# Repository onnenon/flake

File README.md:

<div align="center">
    
    <h3>Anywhy Flake</h3>
    <p><i>Minimalism, efficiency and comfort</i></p>
</div>

# Why

_To be productive, stay healthy and enjoy the process._

By the 19th century, a need for a faster way of writing had emerged, which led to the invention of typewriters. Two centuries later, modern keyboards don't look much different from their predecessors, even though such design has been proven to be quite inefficient and often harmful.

Addressing these problems leads to huge benefits considering how often people use keyboards in the modern world.

# How

There are several problems that the Flake keyboard solves. I'll describe those with the most significant impact.

## Stagger

If you take your hand and look at the fingers, you can notice that they are positioned horizontally. Now take a look at your keyboard - the keys are grouped in arrays that are shifted vertically, known as row-based stagger.

This well-known layout forces your fingers to move in a counterintuitive way. The solution to that problem is simple: we need to rearrange the keys in a more human-friendly way.

As you can see, Flake has what's called a column-based stagger. Because of this, keys are located in the path of natural finger movement, which results in a much more pleasant typing experience and reduced fatigue.

## Split

One of the most noticeable things about Flake is that it has two separate halves.

Regular keyboards are made in a single monolithic block, and the main problem is that such a form factor requires our forearms to meet in the center. To compensate for this, wrists are bent apart. This position creates an unnatural angle between the forearm and the wrist, which in the long term will likely lead to constant wrist pain.

Each half of the split keyboard can be rotated and placed in any suitable way so everyone can adapt the setup to their personal preference, avoiding potential damage to the wrists.

As an added bonus, we get free space right between the halves which can be occupied by a trackpad, coffee, or even a cat (=^..^=).

## Keys amount

There's a high chance that some might feel confused seeing such a small number of keys, considering user productivity is one of the priorities for Anywhy.

Indeed, Flake has fewer keys than most conventional keyboards (46 keys in total), and that's not a compromise, but a feature. A large number of keys causes hands to move around to reach further-placed keys like digits, brackets, punctuation, Backspace, Escape, etc.

Having fewer keys doesn't mean less functionality. In fact, Flake is not only fully input-compatible with regular keyboards but also allows you to add more keys than most keyboards have.

By default, Flake uses [ZMK Firmware](https://zmk.dev) which provides functionality that significantly increases productivity. One of the most used features, which allows having all possible inputs with a minimal amount of keys, is [layers](https://zmk.dev/docs/keymaps#layers). They are pretty simple and work just like the well-known Shift key.

For those who strive for absolute comfort and compactness, there is also Flake S with 40 keys.

The small version lacks one outer column on each of the halves to reduce pinky usage, as it is the weakest of all fingers.

## Thumb cluster

Keyboards are used in various ways, not only for typing text. Most popular tasks require the use of mod keys such as Control, Alt/Option, Super/Command/Win, and of course, Shift. Even though these keys are regularly used, they are placed in ridiculously inconvenient spots where only the pinky can reach them, and as we already know, it's the weakest finger.

The Flake keyboard has a so-called thumb cluster which contains 10 keys in total to address that problem. In contrast, the thumb is one of the strongest fingers and is ideal for holding mod keys.

# What

Flake supports both wired and wireless (Bluetooth) connection, which makes it perfect for both home usage with a PC or portable setup with a laptop, tablet, or even smartphone.

To achieve both types of connectivity, each half has two USB-C ports, one on the top and one on the inner side. The side port is used to connect the halves together, and then one of them (usually the left one) can be connected to any device using the top port, which is also used to charge the keyboard.

> Ports on the side are used only to communicate with each other, so they can't be used to charge the keyboard or to flash the new firmware
> 

Flake is extremely thin. The keyboard body without switches and feet is a bit less than 0.8cm in height, which makes it compact and really comfortable to use, especially with low-profile switches.

> Unfortunately, to achieve such a low height, some tradeoffs were made in PCB and enclosure designs that make assembly and soldering a bit tricky. There's a chance that the keyboard will become thicker in the future if it will make it more robust and easier to repair.

Talking about switches, Flake is hot-swappable and supports three types of switches: the well-known Cherry MX compatible switches, low-profile Kailh Choc V1, and their newer version Choc V2.

In order to use MX Switches, the special "plate" comes with the Flake which should be placed between the board and the switches.

> Plates are not required for the Choc switches as they are much lower than MX switches and don't need additional enclosure height to securely sit in the board

Anywhy Flake v0.1.0 is fully the tested version. The most similar version this repo has is v0.1.1, where I've changed the silkscreen modified some edges, and also added PCB copper fill. So if you want to build Flake yourself, I recommend using the v0.1.1 version, as well as checking out the [build guide](/docs/build_guide.md)

> Feel free to send me your builds and keyboard reviews :)

# Credits

Huge thanks to:

- [@foostan](https://github.com/foostan), the author of [Corne Keyboard](https://github.com/foostan/crkbd) which was my introduction to the world of ergonomic keyboards.
  
- [@pashutk](https://github.com/pashutk), the author of [Chocofi](https://github.com/pashutk/chocofi), an amazing tiny keyboard I've been using for a while.
  
- [@josefadamcik](https://github.com/josefadamcik), the author of [Sofle](https://github.com/josefadamcik/SofleKeyboard) which gave huge inspiration for the Flake's key layout.
  
- [@petejohanson](https://github.com/petejohanson) for creating [ZMK Firmware](https://github.com/zmkfirmware/zmk) and all the [contributors](https://github.com/zmkfirmware/zmk/graphs/contributors) that make it better each day.

- Everyone working on [KiCad](https://gitlab.com/kicad/code/kicad) and [FreeCAD](https://github.com/FreeCAD/FreeCAD), for creating such powerful open source tools

- People from the [ZMK discord server](https://zmk.dev/community/discord/invite) for being so kind while helping me learn how to design PCB and how to debug and solve various problems.

- Finally, a huge thank you to everyone who explores unpopular technologies, digs into niche topics, and makes amazing things possible.

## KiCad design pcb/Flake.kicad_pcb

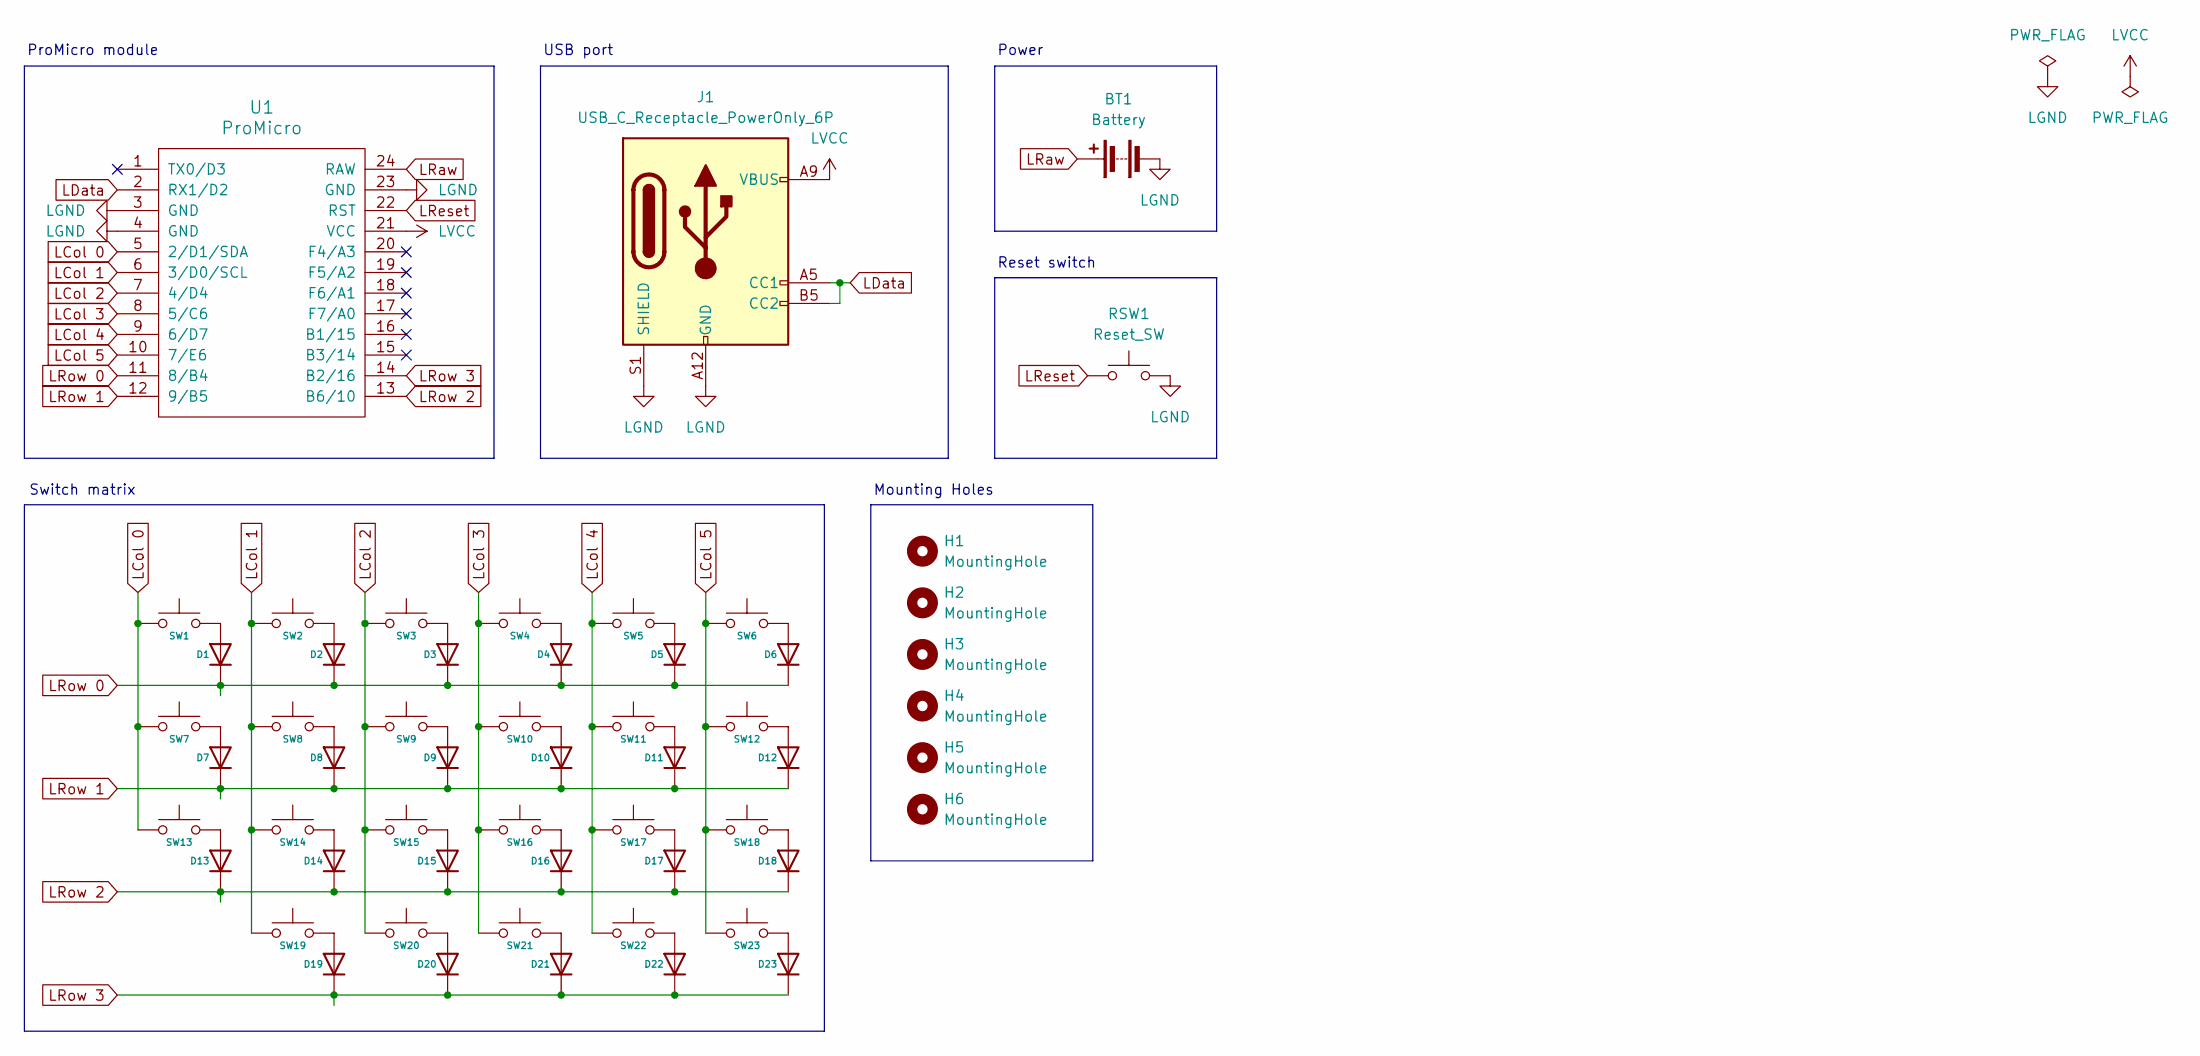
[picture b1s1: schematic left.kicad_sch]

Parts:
BT1: Battery; JST_1.25mm_mid-mount
D1, D2, D3, D4, D5, D6, D7, D8, D9, D10, D11, D12, D13, D14, D15, D16, D17, D18, D19, D20, D21, D22, D23: D; D_SOD-123_Handsoldering
H1, H2, H3, H4, H5, H6: MountingHole; MountingHole_2.2mm_M2
J1: USB_C_Receptacle_PowerOnly_6P; USB-C_6Pin_Mid-mount
RSW1: Reset_SW; TS-1289VE-4
SW1, SW2, SW3, SW4, SW5, SW6, SW7, SW8, SW9, SW10, SW11, SW12, SW13, SW14, SW15, SW16, SW17, SW18, SW19, SW20, SW21, SW22, SW23: SW_Push; SW_MX_Choc-v1v2_Hotswap
U1: ProMicro; ProMicro_SMD

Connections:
LCol 0: SW1.1, SW7.1, SW13.1, U1.5 (2/D1/SDA)
LCol 1: SW2.1, SW8.1, SW14.1, SW19.1, U1.6 (3/D0/SCL)
LCol 2: SW3.1, SW9.1, SW15.1, SW20.1, U1.7 (4/D4)
LCol 3: SW4.1, SW10.1, SW16.1, SW21.1, U1.8 (5/C6)
LCol 4: SW5.1, SW11.1, SW17.1, SW22.1, U1.9 (6/D7)
LCol 5: SW6.1, SW12.1, SW18.1, SW23.1, U1.10 (7/E6)
LData: J1.A5 (CC1), J1.B5 (CC2), U1.2 (RX1/D2)
LGND: BT1.2 (-), J1.A12 (GND), J1.B12 (GND), J1.S1 (SHIELD), RSW1.2, U1.3 (GND), U1.4 (GND), U1.23 (GND)
LRaw: BT1.1 (+), U1.24 (RAW)
LReset: RSW1.1, U1.22 (RST)
LRow 0: D1.1 (K), D2.1 (K), D3.1 (K), D4.1 (K), D5.1 (K), D6.1 (K), U1.11 (8/B4)
LRow 1: D7.1 (K), D8.1 (K), D9.1 (K), D10.1 (K), D11.1 (K), D12.1 (K), U1.12 (9/B5)
LRow 2: D13.1 (K), D14.1 (K), D15.1 (K), D16.1 (K), D17.1 (K), D18.1 (K), U1.13 (B6/10)
LRow 3: D19.1 (K), D20.1 (K), D21.1 (K), D22.1 (K), D23.1 (K), U1.14 (B2/16)
LVCC: J1.A9 (VBUS), J1.B9 (VBUS), U1.21 (VCC)
unnamed: D1.2 (A), SW1.2
unnamed: D2.2 (A), SW2.2
unnamed: D3.2 (A), SW3.2
unnamed: D4.2 (A), SW4.2
unnamed: D5.2 (A), SW5.2
unnamed: D6.2 (A), SW6.2
unnamed: D7.2 (A), SW7.2
unnamed: D8.2 (A), SW8.2
unnamed: D9.2 (A), SW9.2
unnamed: D10.2 (A), SW10.2
unnamed: D11.2 (A), SW11.2
unnamed: D12.2 (A), SW12.2
unnamed: D13.2 (A), SW13.2
unnamed: D14.2 (A), SW14.2
unnamed: D15.2 (A), SW15.2
unnamed: D16.2 (A), SW16.2
unnamed: D17.2 (A), SW17.2
unnamed: D18.2 (A), SW18.2
unnamed: D19.2 (A), SW19.2
unnamed: D20.2 (A), SW20.2
unnamed: D21.2 (A), SW21.2
unnamed: D22.2 (A), SW22.2
unnamed: D23.2 (A), SW23.2

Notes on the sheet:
Switch matrix
Mounting Holes
USB port
Power
ProMicro module
Reset switch

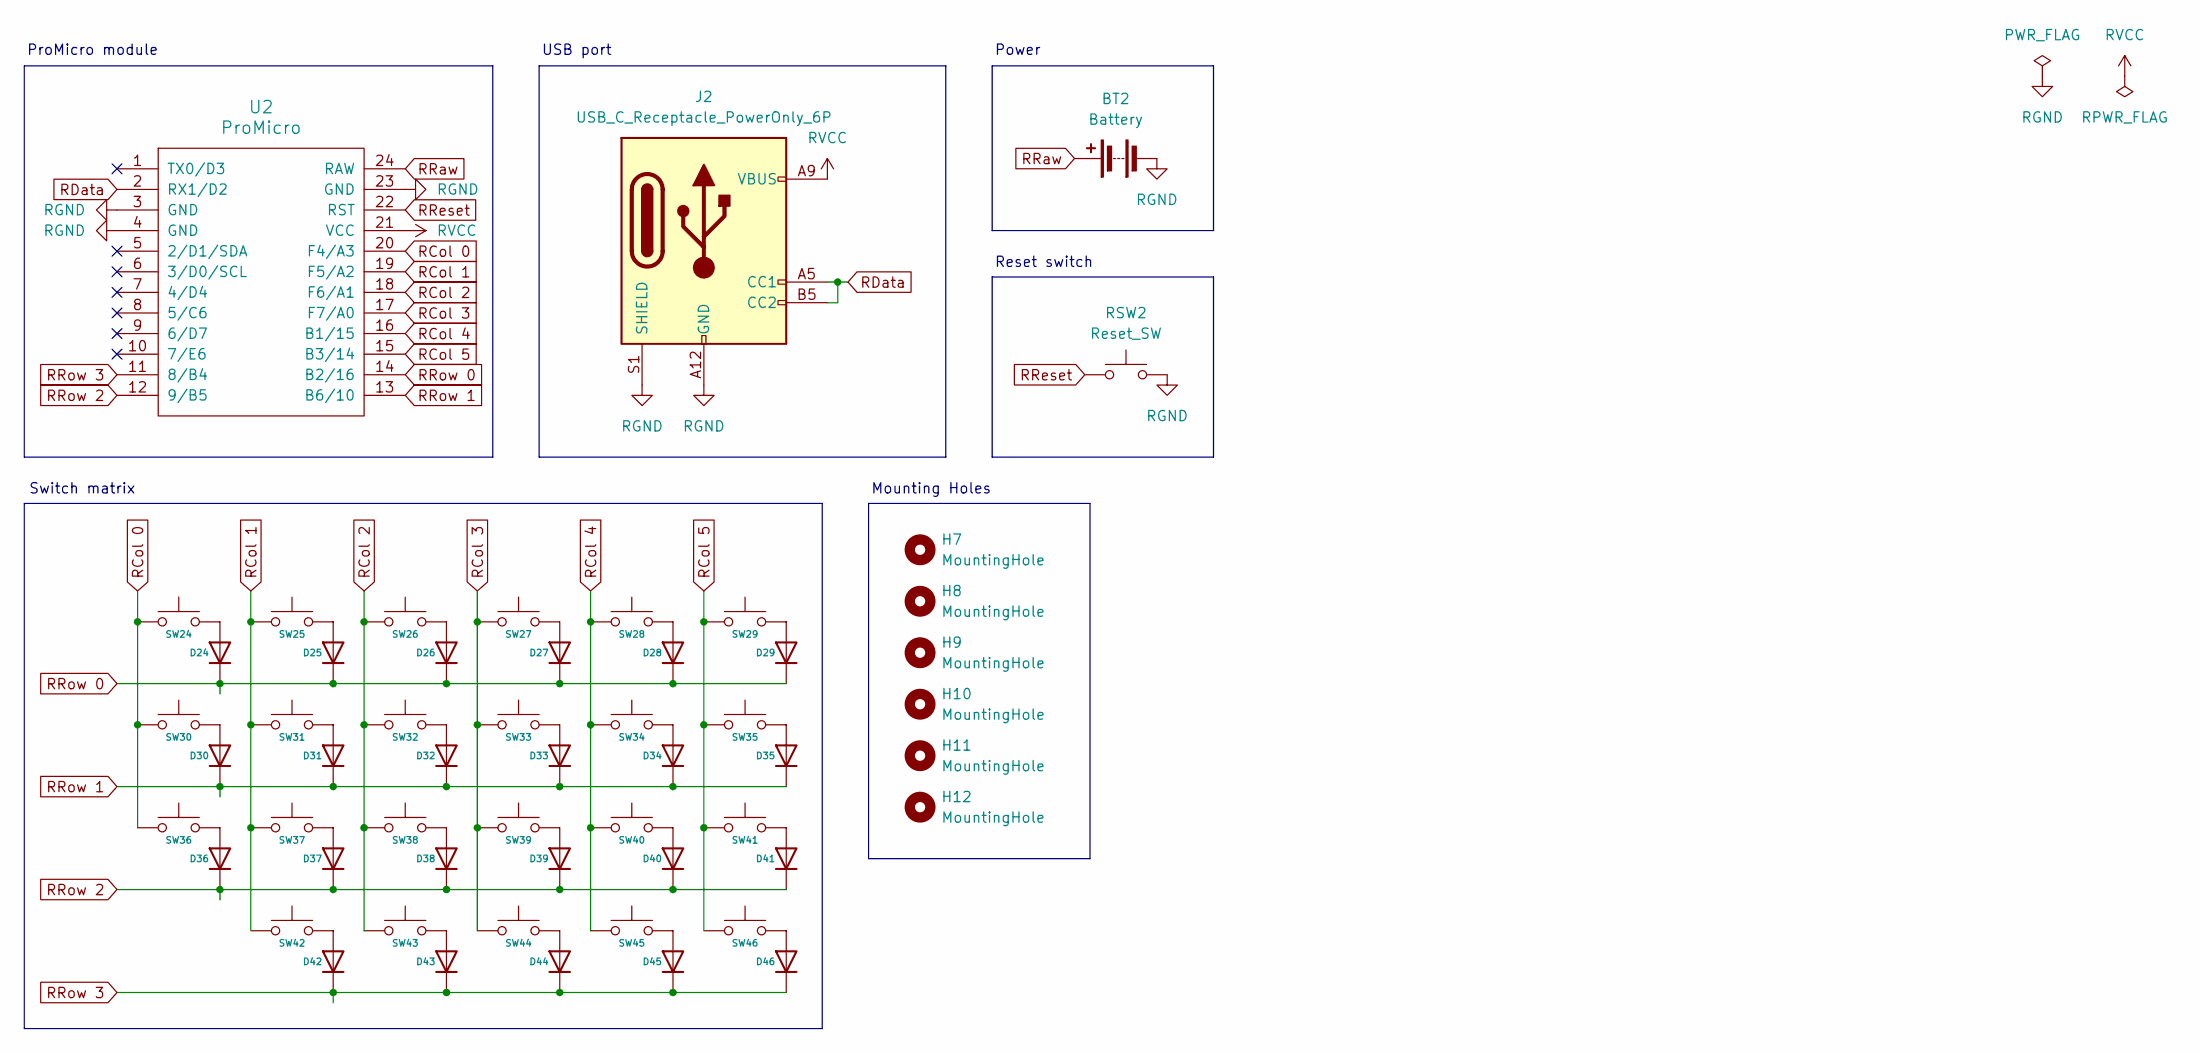
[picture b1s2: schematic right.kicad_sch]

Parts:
BT2: Battery; JST_1.25mm_mid-mount
D24, D25, D26, D27, D28, D29, D30, D31, D32, D33, D34, D35, D36, D37, D38, D39, D40, D41, D42, D43, D44, D45, D46: D; D_SOD-123_Handsoldering
H7, H8, H9, H10, H11, H12: MountingHole; MountingHole_2.2mm_M2
J2: USB_C_Receptacle_PowerOnly_6P; USB-C_6Pin_Mid-mount
RSW2: Reset_SW; TS-1289VE-4
SW24, SW25, SW26, SW27, SW28, SW29, SW30, SW31, SW32, SW33, SW34, SW35, SW36, SW37, SW38, SW39, SW40, SW41, SW42, SW43, SW44, SW45, SW46: SW_Push; SW_MX_Choc-v1v2_Hotswap
U2: ProMicro; ProMicro_SMD

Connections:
unnamed: D24.2 (A), SW24.2
unnamed: D25.2 (A), SW25.2
unnamed: D26.2 (A), SW26.2
unnamed: D27.2 (A), SW27.2
unnamed: D28.2 (A), SW28.2
unnamed: D29.2 (A), SW29.2
unnamed: D30.2 (A), SW30.2
unnamed: D31.2 (A), SW31.2
unnamed: D32.2 (A), SW32.2
unnamed: D33.2 (A), SW33.2
unnamed: D34.2 (A), SW34.2
unnamed: D35.2 (A), SW35.2
unnamed: D36.2 (A), SW36.2
unnamed: D37.2 (A), SW37.2
unnamed: D38.2 (A), SW38.2
unnamed: D39.2 (A), SW39.2
unnamed: D40.2 (A), SW40.2
unnamed: D41.2 (A), SW41.2
unnamed: D42.2 (A), SW42.2
unnamed: D43.2 (A), SW43.2
unnamed: D44.2 (A), SW44.2
unnamed: D45.2 (A), SW45.2
unnamed: D46.2 (A), SW46.2
RCol 0: SW24.1, SW30.1, SW36.1, U2.20 (F4/A3)
RCol 1: SW25.1, SW31.1, SW37.1, SW42.1, U2.19 (F5/A2)
RCol 2: SW26.1, SW32.1, SW38.1, SW43.1, U2.18 (F6/A1)
RCol 3: SW27.1, SW33.1, SW39.1, SW44.1, U2.17 (F7/A0)
RCol 4: SW28.1, SW34.1, SW40.1, SW45.1, U2.16 (B1/15)
RCol 5: SW29.1, SW35.1, SW41.1, SW46.1, U2.15 (B3/14)
RData: J2.A5 (CC1), J2.B5 (CC2), U2.2 (RX1/D2)
RGND: BT2.2 (-), J2.A12 (GND), J2.B12 (GND), J2.S1 (SHIELD), RSW2.2, U2.3 (GND), U2.4 (GND), U2.23 (GND)
RRaw: BT2.1 (+), U2.24 (RAW)
RReset: RSW2.1, U2.22 (RST)
RRow 0: D24.1 (K), D25.1 (K), D26.1 (K), D27.1 (K), D28.1 (K), D29.1 (K), U2.14 (B2/16)
RRow 1: D30.1 (K), D31.1 (K), D32.1 (K), D33.1 (K), D34.1 (K), D35.1 (K), U2.13 (B6/10)
RRow 2: D36.1 (K), D37.1 (K), D38.1 (K), D39.1 (K), D40.1 (K), D41.1 (K), U2.12 (9/B5)
RRow 3: D42.1 (K), D43.1 (K), D44.1 (K), D45.1 (K), D46.1 (K), U2.11 (8/B4)
RVCC: J2.A9 (VBUS), J2.B9 (VBUS), U2.21 (VCC)

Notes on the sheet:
Switch matrix
Mounting Holes
USB port
Power
ProMicro module
Reset switch

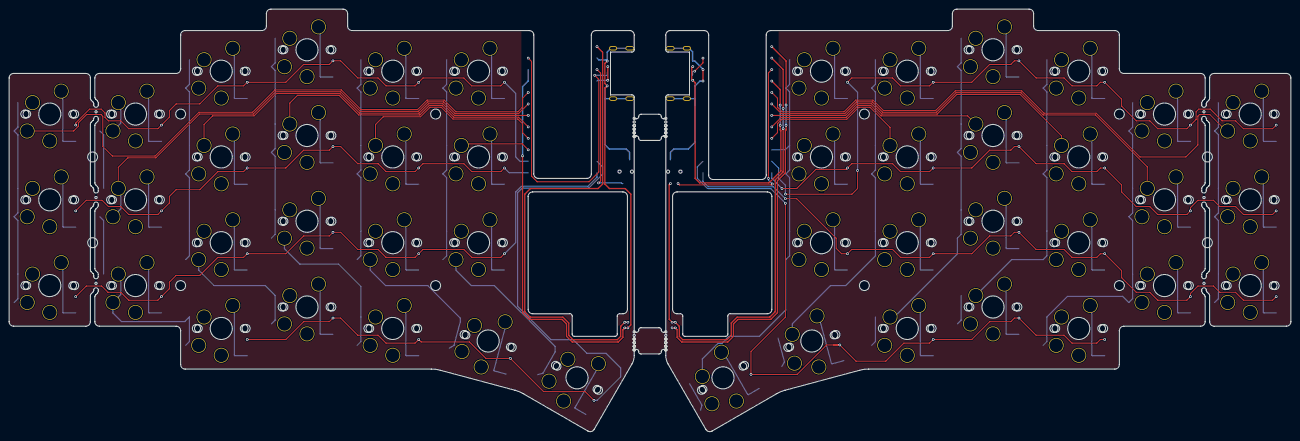
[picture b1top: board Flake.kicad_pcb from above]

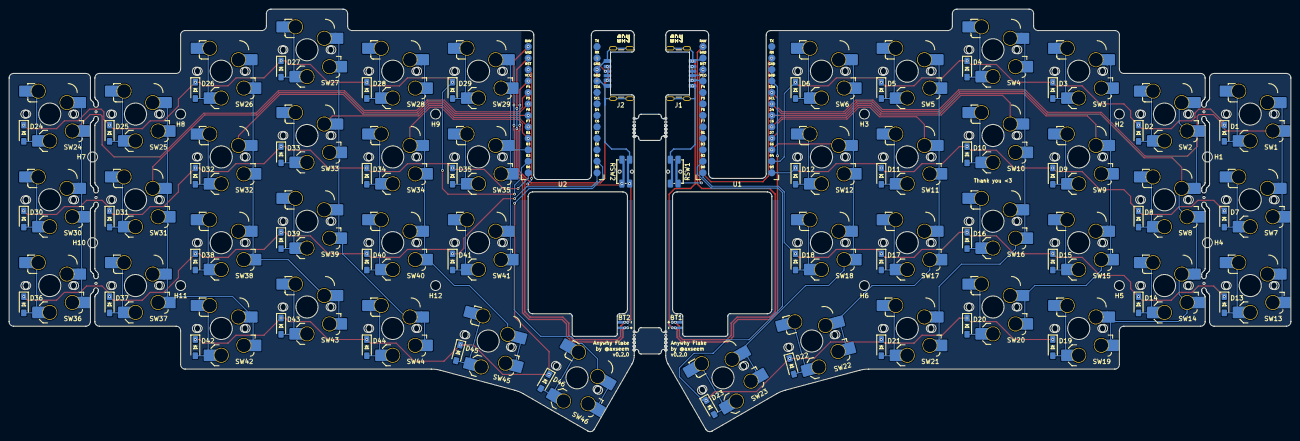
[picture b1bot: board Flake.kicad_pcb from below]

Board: 2 copper layers, 284.0 x 93.6 mm, 112 parts (64 on the bottom side), 76 nets.

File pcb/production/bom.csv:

Designator,Footprint,Quantity,Value,LCSC Part #
"_16, _15, _14, _13, _12, _11, _10, _9, _8, _7, _6, _5, _4, _3, _2, ",,16,,
"BT1, BT2",JST_1.25mm_mid-mount,2,Battery,
"D1, D10, D11, D12, D13, D14, D15, D16, D17, D18, D19, D2, D20, D21, D22, D23, D24, D25, D26, D27, D28, D29, D3, D30, D31, D32, D33, D34, D35, D36, D37, D38, D39, D4, D40, D41, D42, D43, D44, D45, D46, D5, D6, D7, D8, D9",D_SOD-123_Handsoldering,46,D,
"J1, J2",USB-C_6Pin_Mid-mount,2,USB_C_Receptacle_PowerOnly_6P,
"RSW1, RSW2",TS-1289VE-4,2,Reset_SW,
"SW1, SW10, SW11, SW12, SW13, SW14, SW15, SW16, SW17, SW18, SW19, SW2, SW20, SW21, SW22, SW23, SW24, SW25, SW26, SW27, SW28, SW29, SW3, SW30, SW31, SW32, SW33, SW34, SW35, SW36, SW37, SW38, SW39, SW4, SW40, SW41, SW42, SW43, SW44, SW45, SW46, SW5, SW6, SW7, SW8, SW9",SW_MX_Choc-v1v2_Hotswap,46,SW_Push,
"U1, U2",ProMicro_SMD,2,ProMicro,

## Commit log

2024-12-05 init
2024-12-05 docs: remove tautology
2024-12-06 docs: add controller image
2024-12-08 docs: add bill of materials
2024-12-11 pcb: smd controller footprint
    use smd prom-micro footprint
    easier to break off the last column
    wider controller cutout
    ground usb shield
    reroute some paths
    minimse a chance of damaging the pcb after brakeing off the pinky column
2024-12-11 docs: warning about soldering difficulties
